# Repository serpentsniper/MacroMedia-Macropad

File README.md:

# MacroMedia

MacroMedia is a 9 key media macropad with a rotary encoder and an OLED display. It uses KMK firmware on CircuitPython and is built around the Seeed XIAO RP2040.

Built for the Hackpad YSWS through Hack Club Blueprint.

## Features:

* 3x3 key grid for media and productivity controls
* 128x32 OLED display showing an equaliser bars animation
* EC11 rotary encoder for volume control
* 3 layers: Media, DAW shortcuts, and System/Function keys
* Fully 3D printed case
* No LEDs — clean and simple build

## CAD Model:

The case is two pieces — a top plate and a bottom enclosure. Everything is held together with 4 M3x16mm screws and M3x5x4mm heatset inserts.

---

---

The top plate is 1.5mm thick at the switch cutouts so MX switches clip in securely. The encoder shaft and OLED display window are cut into the top section above the key grid.

Made in Autodesk Inventor.
---

---

---

## PCB:

Designed in KiCad. 2-layer board, 59.5mm x 100mm.

---

### Schematic

---

### PCB

---

* 3x3 switch matrix with COL2ROW diode configuration
* Diodes on the back layer, tucked between switch rows
* XIAO RP2040 mounted on the bottom center with USB-C accessible from the rear
* OLED header top-left, encoder top-right
* Ground pour on B.Cu

## Firmware Overview:

This macropad uses [KMK](https://github.com/KMKfw/kmk_firmware) firmware running on CircuitPython.

IMPORTANT NOTE: This macropad's firmware also includes the adafruit\_ssd1306 to interact with the OLED screen. This must be installed into the lib folder on the RP2040.

---

### OLED Animation (concept preview)

---

### Key Mapping

**Layer 0 — Media:**

|Prev|Play/Pause|Next|
|-|-|-|
|Stop|Mute|Vol Up|
|Layer 1|Layer 2|Vol Down|

**Layer 1 — DAW:**

|Undo|Redo|Save|
|-|-|-|
|Cut|Copy|Paste|
|\_\_|\_\_|\_\_|

**Layer 2 — System:**

|F13|F14|F15|
|-|-|-|
|F16|F17|F18|
|\_\_|\_\_|Reset|

**Encoder:** Volume up/down on Layer 0, zoom on Layer 1, brightness on Layer 2.

## BOM:

* 9x Cherry MX Switches
* 9x DSA Keycaps
* 9x 1N4148 DO-35 Diodes
* 1x EC11 Rotary Encoder
* 1x 0.91" 128x32 OLED Display (GND-VCC-SCL-SDA pin order)
* 1x Seeed XIAO RP2040
* 4x M3x16mm Screws
* 4x M3x5x4mm Heatset Inserts
* 1x 3D Printed Case (2 parts: top plate + bottom enclosure)

## Setup:

1. Flash CircuitPython from https://circuitpython.org/board/seeeduino\_xiao\_rp2040
2. Copy `main.py` to your `CIRCUITPY` drive
3. Copy `adafruit\_ssd1306.mpy` to the lib folder in your `CIRCUITPY` drive (accessible at https://github.com/adafruit/Adafruit\_CircuitPython\_SSD1306)

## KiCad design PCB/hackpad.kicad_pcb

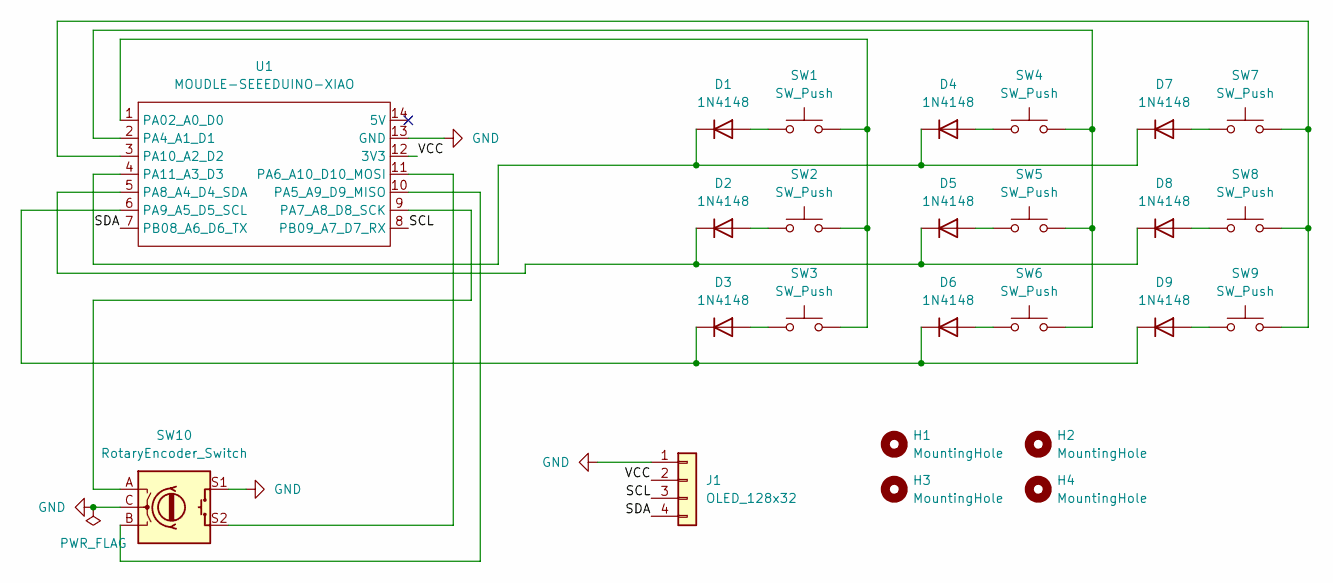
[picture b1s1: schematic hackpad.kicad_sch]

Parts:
D1, D2, D3, D4, D5, D6, D7, D8, D9: 1N4148; D_DO-35_SOD27_P7.62mm_Horizontal
H1, H2, H3, H4: MountingHole; MountingHole_3.2mm_M3
J1: OLED_128x32; SSD1306-0.91-OLED-4pin-128x32
SW1, SW2, SW3, SW4, SW5, SW6, SW7, SW8, SW9: SW_Push; SW_Cherry_MX_1.00u_PCB
SW10: RotaryEncoder_Switch; RotaryEncoder_Alps_EC11E-Switch_Vertical_H20mm
U1: MOUDLE-SEEEDUINO-XIAO; XIAO-Generic-Hybrid-14P-2.54-21X17.8MM

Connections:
/SCL: J1.3, U1.8 (PB09_A7_D7_RX)
/SDA: J1.4, U1.7 (PB08_A6_D6_TX)
/VCC: J1.2, U1.12 (3V3)
GND: J1.1, SW10.C, SW10.S1, U1.13 (GND)
unnamed: D1.2 (A), SW1.1
unnamed: D1.1 (K), D4.1 (K), D7.1 (K), U1.4 (PA11_A3_D3)
unnamed: D2.2 (A), SW2.1
unnamed: D2.1 (K), D5.1 (K), D8.1 (K), U1.5 (PA8_A4_D4_SDA)
unnamed: D3.2 (A), SW3.1
unnamed: D3.1 (K), D6.1 (K), D9.1 (K), U1.6 (PA9_A5_D5_SCL)
unnamed: D4.2 (A), SW4.1
unnamed: D5.2 (A), SW5.1
unnamed: D6.2 (A), SW6.1
unnamed: D7.2 (A), SW7.1
unnamed: D8.2 (A), SW8.1
unnamed: D9.2 (A), SW9.1
unnamed: SW1.2, SW2.2, SW3.2, U1.1 (PA02_A0_D0)
unnamed: SW4.2, SW5.2, SW6.2, U1.2 (PA4_A1_D1)
unnamed: SW10.B, U1.10 (PA5_A9_D9_MISO)
unnamed: SW10.S2, U1.11 (PA6_A10_D10_MOSI)
unnamed: SW10.A, U1.9 (PA7_A8_D8_SCK)
unnamed: SW7.2, SW8.2, SW9.2, U1.3 (PA10_A2_D2)

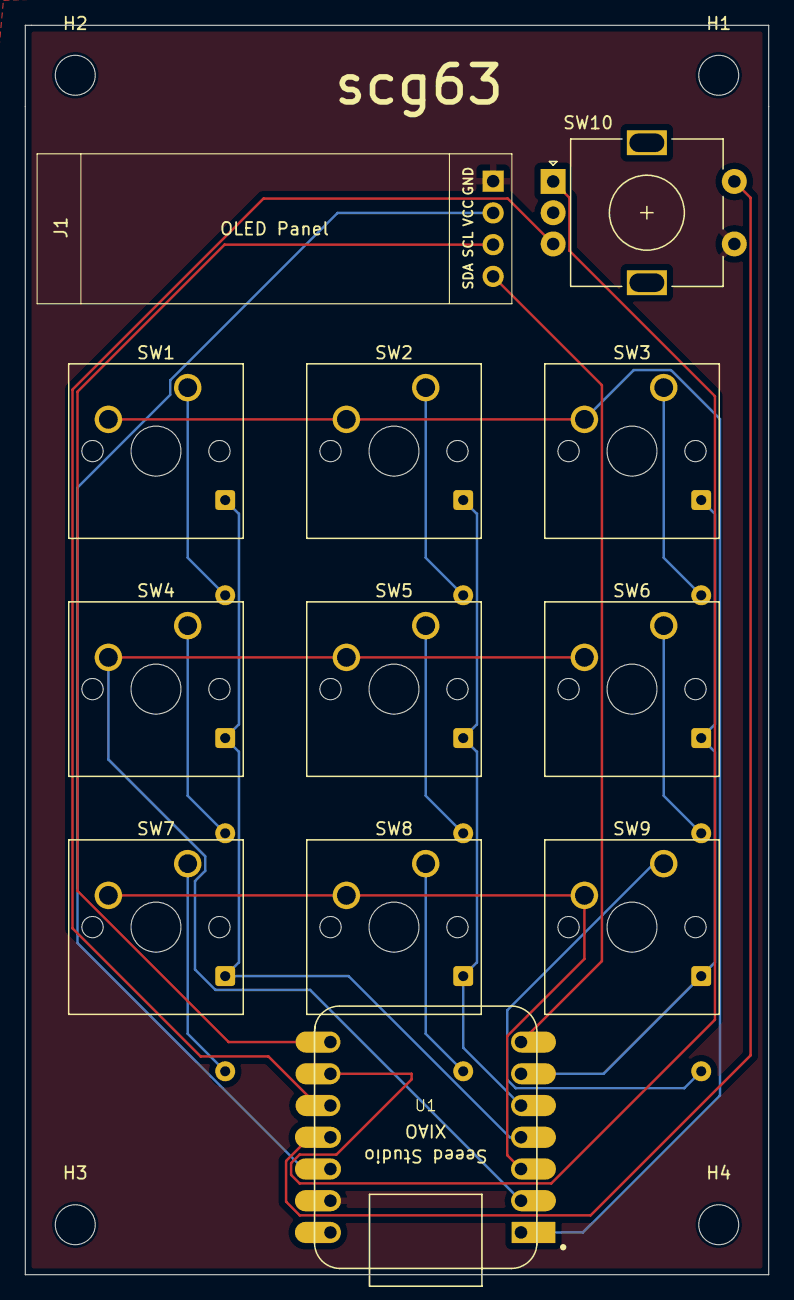
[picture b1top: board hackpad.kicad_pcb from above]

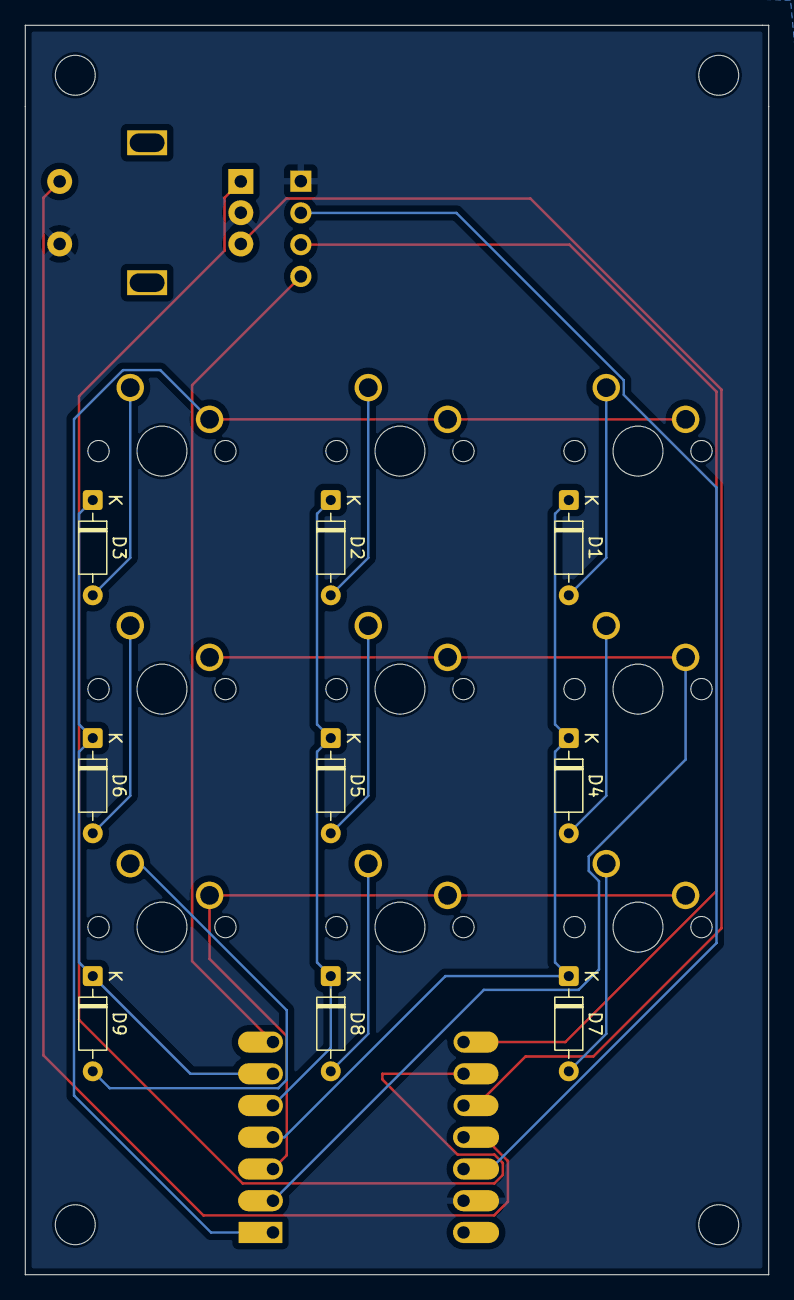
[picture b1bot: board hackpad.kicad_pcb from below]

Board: 2 copper layers, 59.5 x 100.0 mm, 25 parts (9 on the bottom side), 22 nets.

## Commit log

2026-03-06 Added final CAD
2026-03-06 Added all final KiCAD files
2026-03-10 Uploaded CAD files for production
2026-03-10 Added images into README
2026-03-10 Changed project name
2026-06-05 Fix typo in project description
